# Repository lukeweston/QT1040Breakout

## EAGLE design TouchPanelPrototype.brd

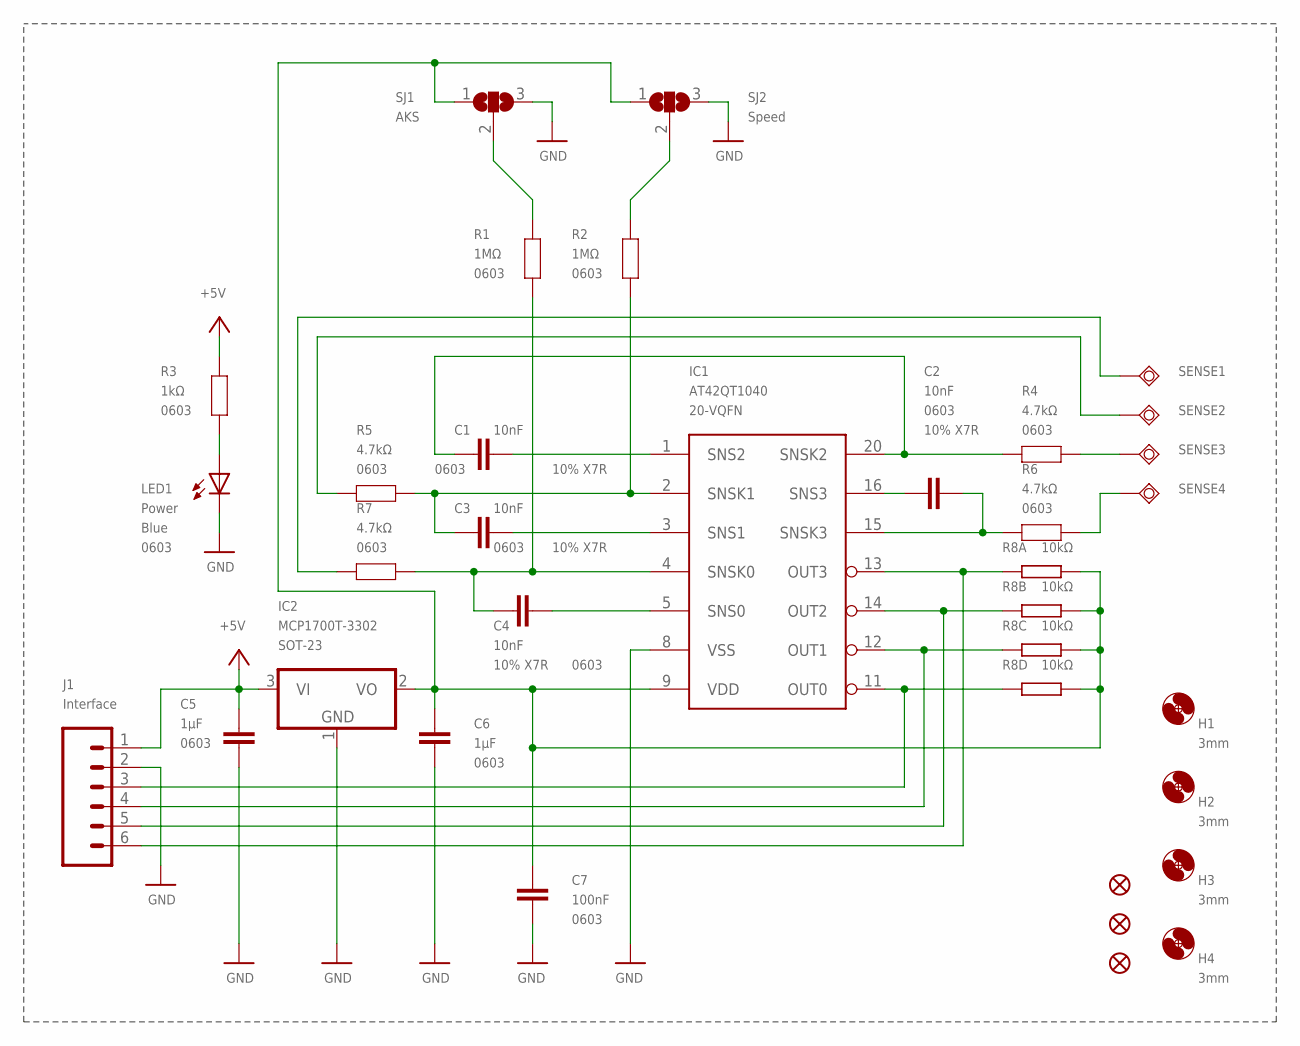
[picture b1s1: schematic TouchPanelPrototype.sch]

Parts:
C1, C2, C3, C4: 10nF; 0603
C5, C6: 1µF; 0603
C7: 100nF; 0603
H1, H2, H3, H4: 3mm; 3,0
IC1: AT42QT1040; QFN/MLF20
IC2: MCP1700T-3302; SOT23
J1: Interface; 1X06
JP1, JP2, JP3: FIDUCIAL1X2; FIDUCIAL-1X2
LED1: Power; LED-0603
R1, R2: 1MΩ; 0603
R3: 1kΩ; 0603
R4, R5, R6, R7: 4.7kΩ; 0603
R8: 10kΩ; CAY16
SENSE1, SENSE2, SENSE3, SENSE4: TPSQTP20R; TP20R
SJ1: AKS; SJ_2
SJ2: Speed; SJ_2

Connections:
+5V: C5.2, IC2.3 (VI), J1.1, R3.1
GND: C5.1, C6.1, C7.1, IC1.8 (VSS), IC2.1 (GND), J1.2, LED1.C, SJ1.3, SJ2.3
unnamed: LED1.A, R3.2
unnamed: C4.1, IC1.5 (SNS0)
unnamed: C2.2, IC1.16 (SNS3)
unnamed: C3.1, IC1.3 (SNS1)
unnamed: C1.1, IC1.1 (SNS2)
unnamed: C1.2, IC1.20 (SNSK2), R4.2
unnamed: C3.2, IC1.2 (SNSK1), R2.2, R5.1
unnamed: C4.2, IC1.4 (SNSK0), R1.2, R7.1
unnamed: C2.1, IC1.15 (SNSK3), R6.2
unnamed: R5.2, SENSE2.TP
unnamed: R4.1, SENSE3.TP
unnamed: R6.1, SENSE4.TP
unnamed: R7.2, SENSE1.TP
unnamed: R1.1, SJ1.2
unnamed: R2.1, SJ2.2
unnamed: C6.2, C7.2, IC1.9 (VDD), IC2.2 (VO), R8.1, R8.2 (1), R8.3 (1), R8.4 (1), SJ1.1, SJ2.1
TOUCH1: IC1.11 (OUT0), J1.3, R8.5 (2)
TOUCH2: IC1.12 (OUT1), J1.4, R8.6 (2)
TOUCH3: IC1.14 (OUT2), J1.5, R8.7 (2)
TOUCH4: IC1.13 (OUT3), J1.6, R8.8 (2)

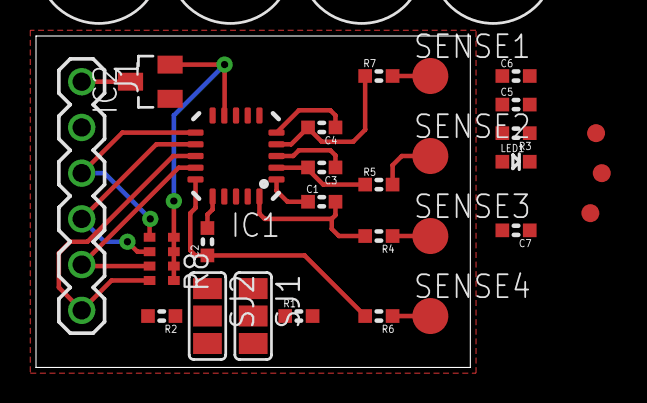
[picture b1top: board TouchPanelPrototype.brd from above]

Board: 2 copper layers, 24.1 x 18.4 mm, 32 parts (0 on the bottom side), 22 nets.
